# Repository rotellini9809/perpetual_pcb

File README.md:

<h1 align="center">Perpetual — Rocket Avionics PCB</h1>

<p align="center">
  A compact RP2350-based flight computer with an IMU, a barometer, 16 MB of flash for flight logs,<br>
  Bluetooth, four pyrotechnic channels and four servo outputs.
</p>

<p align="center">

</p>

---

> **Part of the Perpetual project**, developed for the
> **Sapienza Rocket Team Training Academy**.
>
> | Repository | Contents |
> |---|---|
> | [Perpetual_training_accademy_avionics](https://github.com/Sapienza-Rocket-Team/Perpetual_training_accademy_avionics) | Main project: overview of the whole system, with the two repositories below as submodules |
> | **perpetual_pcb** (this repository) | Hardware: KiCad schematics, PCB layout and fabrication files |
> | [perpetual_code](https://github.com/rotellini9809/perpetual_code) | Firmware and desktop app |

> [!WARNING]
> This board switches **pyrotechnic channels** directly from the battery. Never connect
> igniters or energetics during bench work, and follow your team's and range's safety rules.
> The board has been assembled and bench-tested, but it is **not flight-qualified or certified for
> any use**. Validate any modified version yourself.

## Contents

- [Hardware overview](#hardware-overview)
- [Gallery](#gallery)
- [Connectors](#connectors)
- [Power](#power)
- [Pyro channels](#pyro-channels)
- [Servo power configuration](#servo-power-configuration)
- [Mechanical](#mechanical)
- [Programming](#programming)
- [Repository layout](#repository-layout)
- [Manufacturing](#manufacturing)
- [Development](#development)
- [Author and license](#author-and-license)

## Hardware overview

| Subsystem | Component | Purpose |
| --- | --- | --- |
| Microcontroller | Waveshare RP2350 Tiny | Processing and peripheral control |
| IMU | LSM6DSV32X | 3-axis acceleration (±32 g) and angular rate |
| Barometer | BMP581 | Pressure and temperature, for altitude |
| Storage | W25Q128JV | 16 MB SPI NOR flash for flight logs |
| Wireless | JDY-34 | Bluetooth link to the Perpetual app |
| Pyro channels | 4 × AO3400A, 74LVC08, TPW4054 | Low-side igniter switches gated by a shared hardware enable, with continuity sensing |
| Servo outputs | 74HCT126 buffer | 4 buffered servo signals, with the supply selectable per channel |
| Power | TPS54302 | 5 V / 3 A buck converter |
| Protection | P-MOSFET and SMBJ15CA TVS | Reverse-polarity and transient protection on the battery input |

The board also provides battery-voltage monitoring, an RGB status LED, a JST connector for
telemetry or I2C, and USB through the RP2350 Tiny flex cable. No magnetometer is fitted.

Flight logs are stored in the onboard flash and downloaded with the
[Perpetual app](https://github.com/rotellini9809/perpetual_code) over **USB or Bluetooth**. No
microSD card is needed.

## Gallery

<table>
  <tr>
    <th>Front</th>
    <th>Back</th>
  </tr>
  <tr>
    <td></td>
    <td></td>
  </tr>
</table>

## Connectors

| Ref | Connector | Signals | Notes |
| --- | --- | --- | --- |
| J6 | AMASS XT30 | Battery `+` / GND | Main power input, 2S–3S LiPo |
| J7–J10 | WAGO 2060 push-in, 2-pole | `+BATT` / switched output | Pyro channels 1–4 |
| J4, J5 | 2×3 pin header, 2.54 mm, right-angle | GND, supply, signal | Servos 1–2 and 3–4. Supply chosen per channel, see [below](#servo-power-configuration) |
| J2 | JST-XH, 3-pin | GND, GP19 (RX / SCL), GP18 (TX / SDA) | Telemetry UART or external I2C |
| J3 | 1×3 pin header, 2.54 mm | GND, +3.3 V, +5 V | Auxiliary power for external devices |
| — | RP2350 Tiny FPC | USB | Programming and data, through the flex cable adapter |

The firmware's GPIO assignment for every signal is listed in the firmware's
[hardware reference](https://github.com/rotellini9809/perpetual_code/blob/main/docs/HARDWARE.md).

## Power

The board is designed to run from a **2S or 3S LiPo** battery (about 6–12.6 V) connected to the
XT30 input. The battery path is:

1. **SMBJ15CA TVS** (D3) across the raw input, for transients. Its 15 V stand-off sets the
   practical upper limit of the input; do not exceed 3S.
2. **P-MOSFET** (Q1, 30P20M) for reverse-polarity protection, giving the protected `+BATT` rail.
3. **TPS54302** buck converter (U4): 5 V rail, up to 3 A.

The RP2350 Tiny provides the 3.3 V rail. Its VSYS input is fed from the 5 V rail through a
**B5817W Schottky** (D1), so USB power cannot back-feed the 5 V rail: on USB alone the MCU and
sensors run, but the servo buffer, servos and pyro channels have no supply. The battery voltage is
measured by the MCU through a 100 kΩ / 24 kΩ divider.

## Pyro channels

Each channel is a WAGO 2060 push-in terminal between `+BATT` and the drain of an **AO3400A**
low-side MOSFET (Q2–Q5). The MOSFET gates are driven by a **74LVC08** AND gate (U6) that combines
the channel pin with a shared **enable** pin: a channel only conducts while both are high, so a
single stuck GPIO cannot fire it. A **TPW4054** 4:1 analog multiplexer (U5) lets the MCU read the
continuity of one channel at a time on an ADC pin.

The firmware's GPIO assignment, firing sequence and continuity thresholds are in the firmware's
[hardware reference](https://github.com/rotellini9809/perpetual_code/blob/main/docs/HARDWARE.md#board-circuits).

## Servo power configuration

Each of the four servo outputs has its own solder bridge on the back of the PCB. The bridge
connects that servo's supply pin either to the regulated **5 V** rail or to the **+BATT** rail.

To configure a channel:

1. Disconnect all power sources.
2. Find the bridge for that channel (**1–4**) using the board markings.
3. Solder **only one side**, toward **5V** or **+BATT**.
4. Check the connection and measure the output voltage before plugging in the servo.

> [!CAUTION]
> With **+BATT** the servo receives the full battery voltage, which must be within the servo's
> rated supply range.

## Mechanical

| Dimension | Value |
| --- | --- |
| Board outline | 50 × 80 mm, 3 mm corner radius |
| Thickness | 1.6 mm, 4 layers |
| Mounting holes | 4 × Ø2.7 mm for M2.5 screws, one per corner |
| Hole position | Centres 3.5 mm from each board edge |
| Hole spacing | 43 × 73 mm, centre to centre |

Pyro terminals sit on one short edge, and the servo headers and XT30 on the other. Leave room
beside the XT30 and the push-in terminals for the cables.

**Bench stand.** A printable stand that holds the board still for IMU calibration and bench tests
is in [`mechanical/bench-stand/`](mechanical/bench-stand). It fixes the board on its four mounting
holes with M2.5 screws.

## Programming

The board is programmed over USB through the **flex cable and USB-C adapter board** supplied
with the Waveshare RP2350 Tiny. The adapter plugs into the FPC connector of the RP2350 Tiny
module, so the main PCB needs no USB connector of its own.

**Perpetual firmware.** The flight computer firmware is in
[perpetual_code](https://github.com/rotellini9809/perpetual_code) and is built and uploaded with
PlatformIO. Connect the adapter with the flex cable (contacts on the correct side), then from that
repository run:

```powershell
pio run -t upload
```

If the board is not detected, hold **BOOT** while plugging in the USB cable, then upload again.
See the [firmware quick start](https://github.com/rotellini9809/perpetual_code#quick-start).

**Your own firmware.** For the MCU, Perpetual is a standard RP2350 Tiny, so you can flash it like
any RP2350 board: with the Pico SDK, Arduino-Pico, MicroPython, or by holding **BOOT** while
plugging in USB and copying a `.uf2` file to the `RP2350` drive that appears. For the pin
assignment, see the firmware's
[hardware reference](https://github.com/rotellini9809/perpetual_code/blob/main/docs/HARDWARE.md),
and for the module, the bootloader and the adapter board, see the
[Waveshare RP2350-Tiny wiki](https://www.waveshare.com/wiki/RP2350-Tiny).

## Repository layout

| Path | Contents |
| --- | --- |
| `perpetual_pcb.kicad_pro` | KiCad project: open this file |
| `perpetual_pcb.kicad_sch` | Top-level schematic, with the `power`, `pyro`, `sensors` and `memory` sub-sheets |
| `perpetual_pcb.kicad_pcb` | PCB layout (4 layers) |
| [`libs/`](libs) | Project symbols, footprints and 3D models |
| [`fabrication_files/`](fabrication_files) | Gerber and drill files |
| [`bom/`](bom) | Interactive BOM (`ibom.html`) |
| [`mechanical/`](mechanical) | 3D-printable parts: the bench stand |
| [`docs/`](docs) | Images, mechanical drawing and component datasheets |

## Manufacturing

Ready-to-order **Gerber and drill files** are in [`fabrication_files/`](fabrication_files), and
also zipped as [`fabrication_files.zip`](fabrication_files.zip). The board is a **4-layer** PCB.
Upload the zip to your PCB manufacturer, and check that the files match the revision you intend
to build.

An interactive bill of materials with component placement is in [`bom/ibom.html`](bom/ibom.html):
download it and open it in a browser.

## Development

Open `perpetual_pcb.kicad_pro` in KiCad 10 to inspect or modify the schematic and the layout.
Before manufacturing or powering a board, review the component ratings, the connections and the
hardware revision.

Contributions and derivatives are welcome within the terms of the license. Please document
meaningful hardware changes and how you validated them.

## Author and license

Designed by **Simone Cargnin** ([@rotellini9809](https://github.com/rotellini9809)) for the
**Sapienza Rocket Team Training Academy**.

Copyright © 2026 Simone Cargnin.

Except where otherwise noted, the original hardware design files and documentation in this
repository are licensed under
[Creative Commons Attribution-NonCommercial-ShareAlike 4.0 International](LICENSE).

When sharing these files or adaptations, give appropriate credit, link to the license and
indicate your changes. Shared adaptations must use CC BY-NC-SA 4.0, a later version, or a
BY-NC-SA Compatible License.

Suggested attribution:
“Based on Perpetual by Simone Cargnin, developed for the Sapienza Rocket Team Training Academy.”
Original project: https://github.com/rotellini9809/perpetual_pcb

Third-party symbols, footprints, models and other assets keep their own licenses.

For commercial permissions, contact rotellini9809@gmail.com.

If you use Perpetual in research, please let me know at the address above. This is a voluntary
request, not a license condition.

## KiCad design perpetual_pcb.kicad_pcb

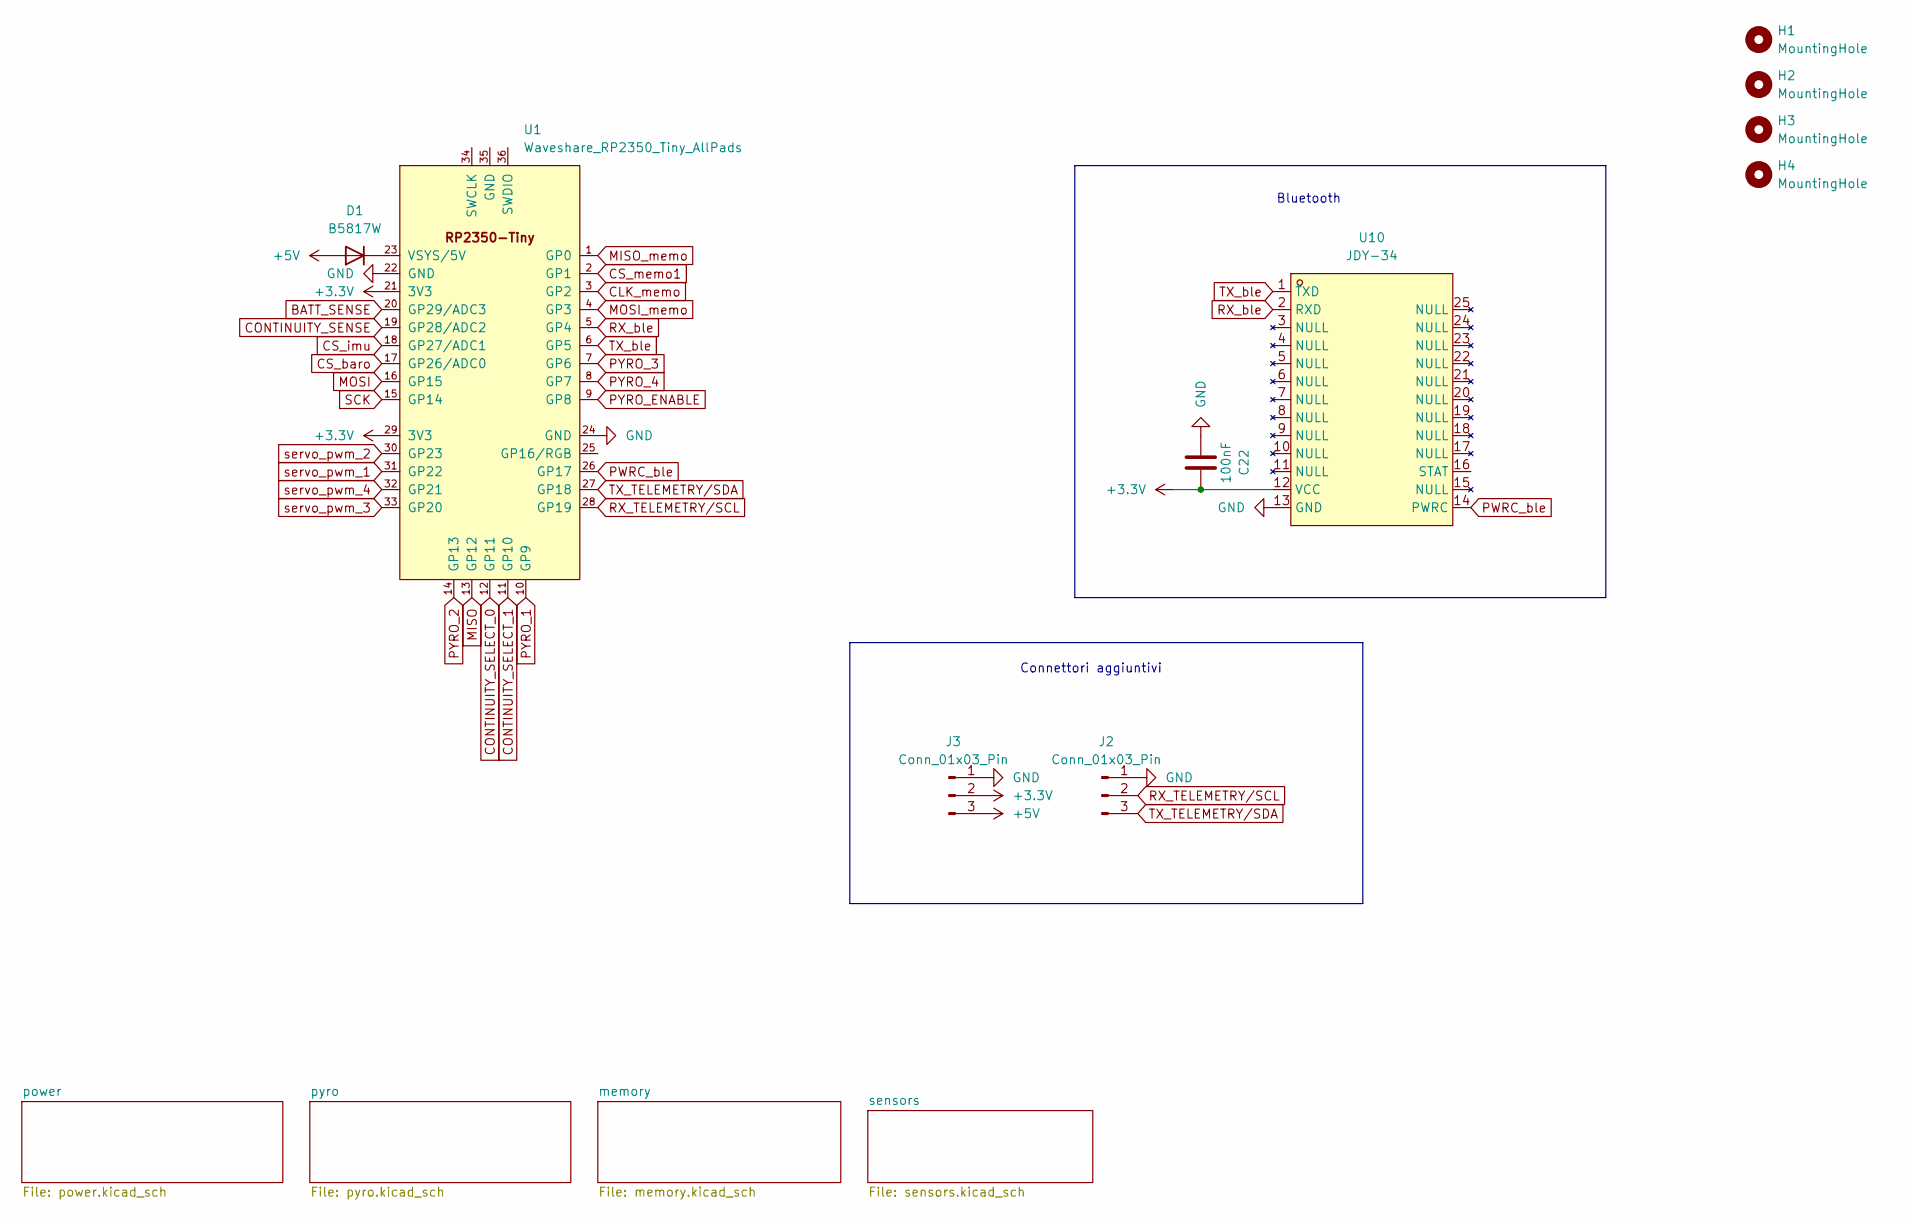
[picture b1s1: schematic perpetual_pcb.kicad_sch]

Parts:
C22: 100nF; C_0603_1608Metric
D1: B5817W; D_SOD-123
H1, H2, H3, H4: MountingHole; MountingHole_2.7mm_M2.5
J2: Conn_01x03_Pin; JST_XH_B3B-XH-A_1x03_P2.50mm_Vertical
J3: Conn_01x03_Pin; PinHeader_1x03_P2.54mm_Vertical
U1: Waveshare_RP2350_Tiny_AllPads; Waveshare_RP2350_Tiny_AllPads_36Pin
U10: JDY-34; BULETM-SMD_JDY-34; MPN JDY-34

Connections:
+3.3V: C22.1, J3.2, U1.21 (3V3), U1.29 (3V3), U10.12 (VCC); also elsewhere on the board
+5V: D1.2 (A), J3.3; also elsewhere on the board
BATT_SENSE: U1.20 (GP29/ADC3); also elsewhere on the board
CLK_memo: U1.3 (GP2); also elsewhere on the board
CONTINUITY_SELECT_0: U1.12 (GP11); also elsewhere on the board
CONTINUITY_SELECT_1: U1.11 (GP10); also elsewhere on the board
CONTINUITY_SENSE: U1.19 (GP28/ADC2); also elsewhere on the board
CS_baro: U1.17 (GP26/ADC0); also elsewhere on the board
CS_imu: U1.18 (GP27/ADC1); also elsewhere on the board
CS_memo1: U1.2 (GP1); also elsewhere on the board
GND: C22.2, J2.1, J3.1, U1.22 (GND), U1.24 (GND), U10.13 (GND); also elsewhere on the board
MISO: U1.13 (GP12); also elsewhere on the board
MISO_memo: U1.1 (GP0); also elsewhere on the board
MOSI: U1.16 (GP15); also elsewhere on the board
MOSI_memo: U1.4 (GP3); also elsewhere on the board
unnamed: D1.1 (K), U1.23 (VSYS/5V)
PWRC_ble: U1.26 (GP17), U10.14 (PWRC)
PYRO_1: U1.10 (GP9); also elsewhere on the board
PYRO_2: U1.14 (GP13); also elsewhere on the board
PYRO_3: U1.7 (GP6); also elsewhere on the board
PYRO_4: U1.8 (GP7); also elsewhere on the board
PYRO_ENABLE: U1.9 (GP8); also elsewhere on the board
RX_TELEMETRY/SCL: J2.2, U1.28 (GP19)
RX_ble: U1.5 (GP4), U10.2 (RXD)
SCK: U1.15 (GP14); also elsewhere on the board
TX_TELEMETRY/SDA: J2.3, U1.27 (GP18)
TX_ble: U1.6 (GP5), U10.1 (TXD)
servo_pwm_1: U1.31 (GP22); also elsewhere on the board
servo_pwm_2: U1.30 (GP23); also elsewhere on the board
servo_pwm_3: U1.33 (GP20); also elsewhere on the board
servo_pwm_4: U1.32 (GP21); also elsewhere on the board

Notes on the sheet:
Bluetooth
Connettori aggiuntivi

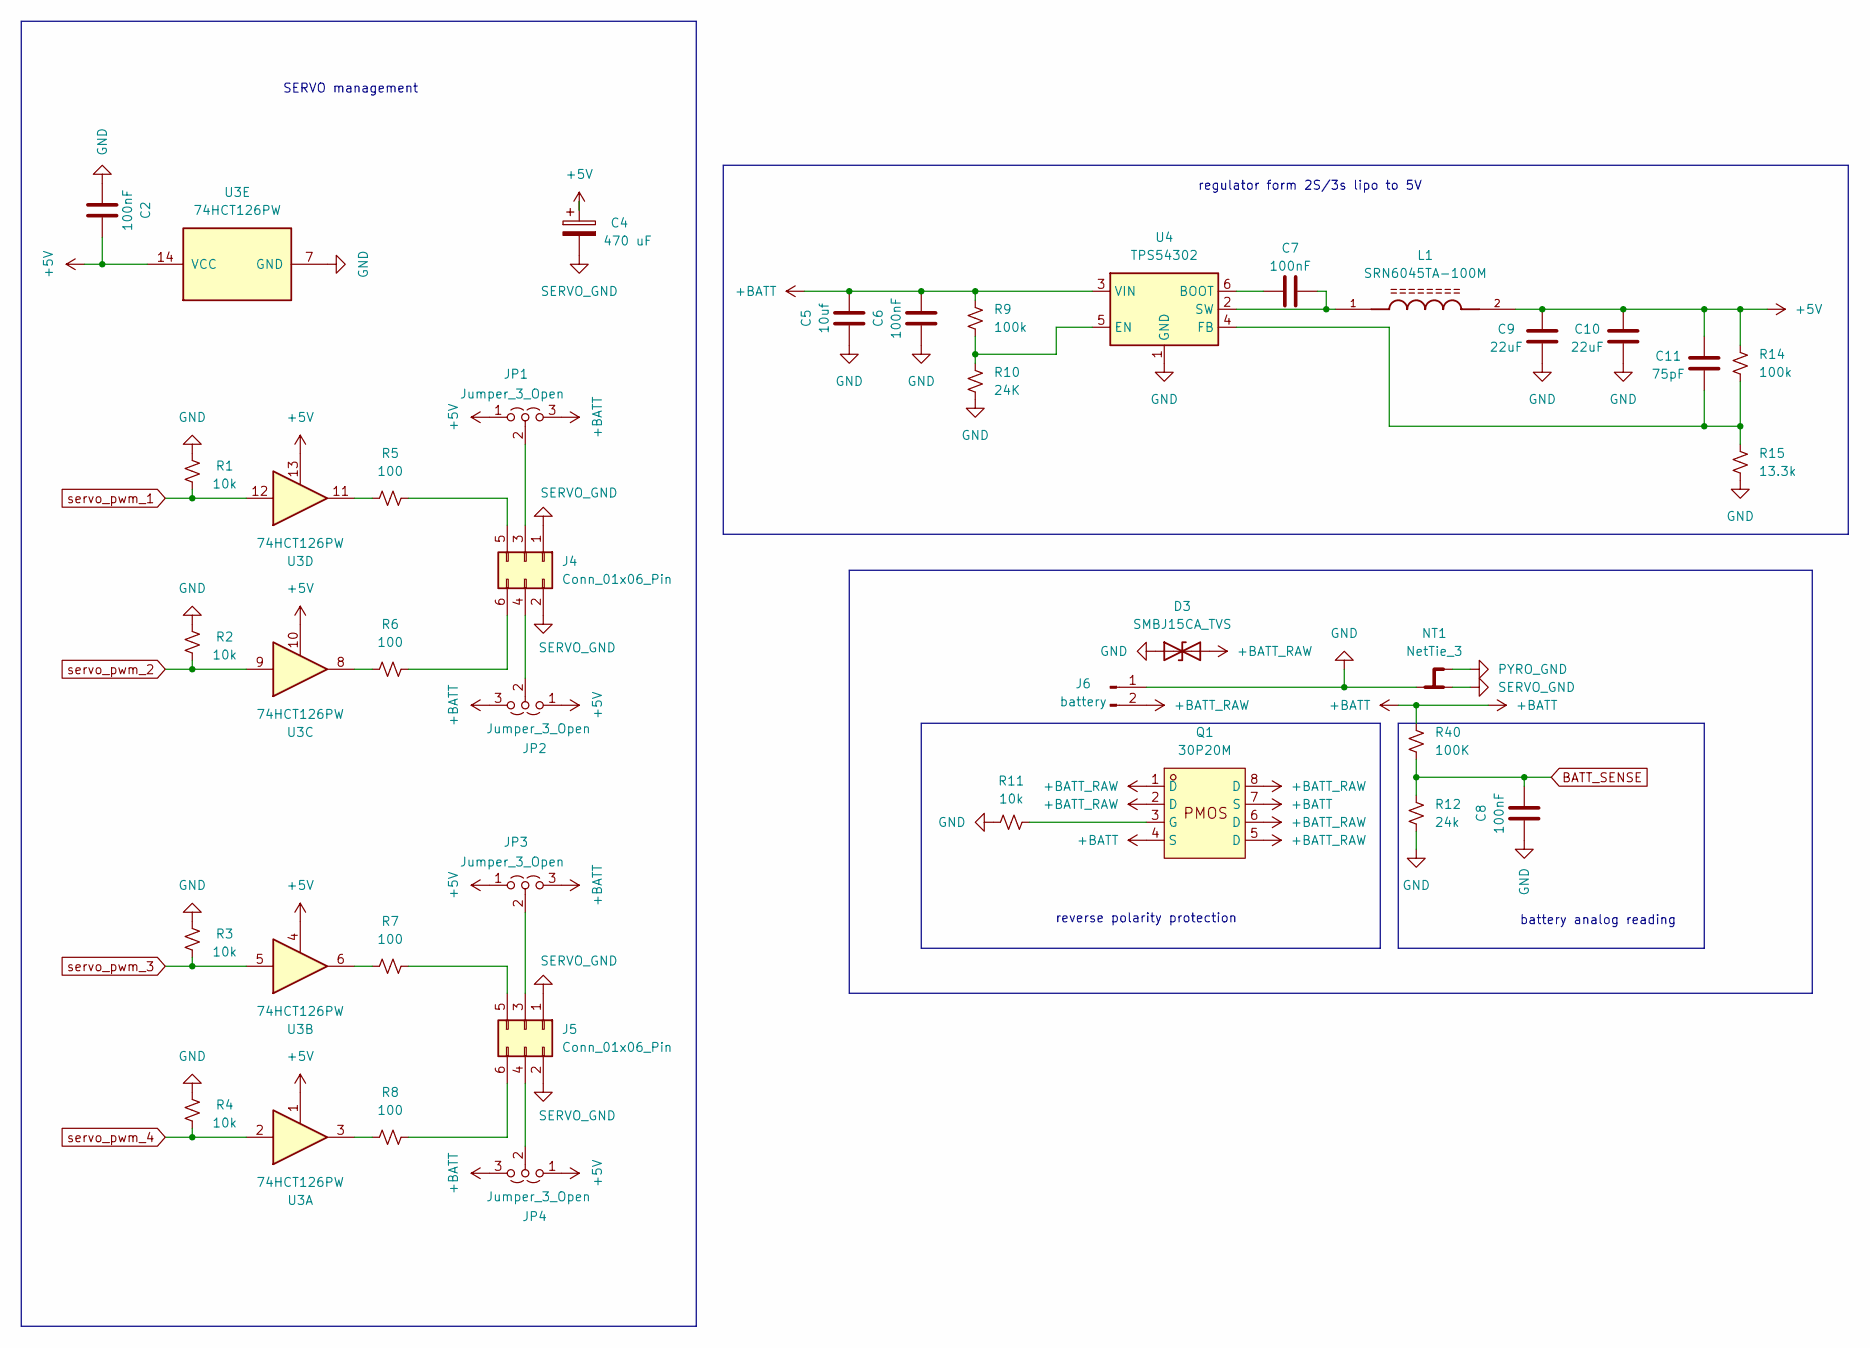
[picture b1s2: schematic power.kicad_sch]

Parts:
C2, C6, C7, C8: 100nF; C_0603_1608Metric
C4: 470 uF; C_Elec_8x10.2; LCSC part C141429
C5: 10uf; C_1206_3216Metric
C9, C10: 22uF; C_1206_3216Metric
C11: 75pF; C_0603_1608Metric
D3: SMBJ15CA_TVS; D_SMB
J4, J5: Conn_01x06_Pin; PinHeader_2x03_P2.54mm_Horizontal
J6: battery; AMASS_XT30PW-M_1x02_P2.50mm_Horizontal
JP1, JP2, JP3, JP4: Jumper_3_Open; SolderJumper-3_P1.3mm_Open_RoundedPad1.0x1.5mm
L1: SRN6045TA-100M
NT1: NetTie_3; NetTie-3_SMD_Pad2.0mm
Q1: 30P20M; MPN 30P20M; LCSC Part C7471110
R1, R2, R3, R4, R11: 10k; R_0603_1608Metric
R5, R6, R7, R8: 100; R_0603_1608Metric
R9, R14: 100k; R_0603_1608Metric
R10: 24K; R_0603_1608Metric
R12: 24k; R_0603_1608Metric
R15: 13.3k; R_0603_1608Metric
R40: 100K; R_0603_1608Metric
U3: 74HCT126PW; TSSOP-14_4.4x5mm_P0.65mm
U4: TPS54302; SOT-23-6

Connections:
+5V: C2.1, C4.1, C9.1, C10.1, C11.1, JP1.1 (A), JP2.1 (A), JP3.1 (A), JP4.1 (A), L1.2, R14.1, U3.1, U3.4, U3.10, U3.13, U3.14 (VCC); also elsewhere on the board
+BATT: C5.1, C6.1, JP1.3 (B), JP2.3 (B), JP3.3 (B), JP4.3 (B), Q1.4 (S), Q1.7 (S), R9.1, R40.1, U4.3 (VIN); also elsewhere on the board
+BATT_RAW: D3.2 (A2), J6.2, Q1.1 (D), Q1.2 (D), Q1.5 (D), Q1.6 (D), Q1.8 (D)
BATT_SENSE: C8.1, R12.1, R40.2; also elsewhere on the board
GND: C2.2, C5.2, C6.2, C8.2, C9.2, C10.2, D3.1 (A1), J6.1, NT1.2, R1.1, R2.1, R3.1, R4.1, R10.2, R11.1, R12.2, R15.2, U3.7 (GND), U4.1 (GND); also elsewhere on the board
unnamed: J4.3, JP1.2 (C)
unnamed: J4.4, JP2.2 (C)
unnamed: J4.5, R5.2
unnamed: J4.6, R6.2
unnamed: J5.3, JP3.2 (C)
unnamed: J5.4, JP4.2 (C)
unnamed: J5.5, R7.2
unnamed: J5.6, R8.2
unnamed: Q1.3 (G), R11.2
unnamed: R5.1, U3.11
unnamed: R6.1, U3.8
unnamed: R7.1, U3.6
unnamed: R8.1, U3.3
unnamed: C7.2, U4.6 (BOOT)
unnamed: R9.2, R10.1, U4.5 (EN)
unnamed: C11.2, R14.2, R15.1, U4.4 (FB)
unnamed: C7.1, L1.1, U4.2 (SW)
PYRO_GND: NT1.3; also elsewhere on the board
SERVO_GND: C4.2, J4.1, J4.2, J5.1, J5.2, NT1.1
servo_pwm_1: R1.2, U3.12; also elsewhere on the board
servo_pwm_2: R2.2, U3.9; also elsewhere on the board
servo_pwm_3: R3.2, U3.5; also elsewhere on the board
servo_pwm_4: R4.2, U3.2; also elsewhere on the board

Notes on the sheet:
regulator form 2S/3s lipo to 5V
reverse polarity protection
SERVO management
battery analog reading

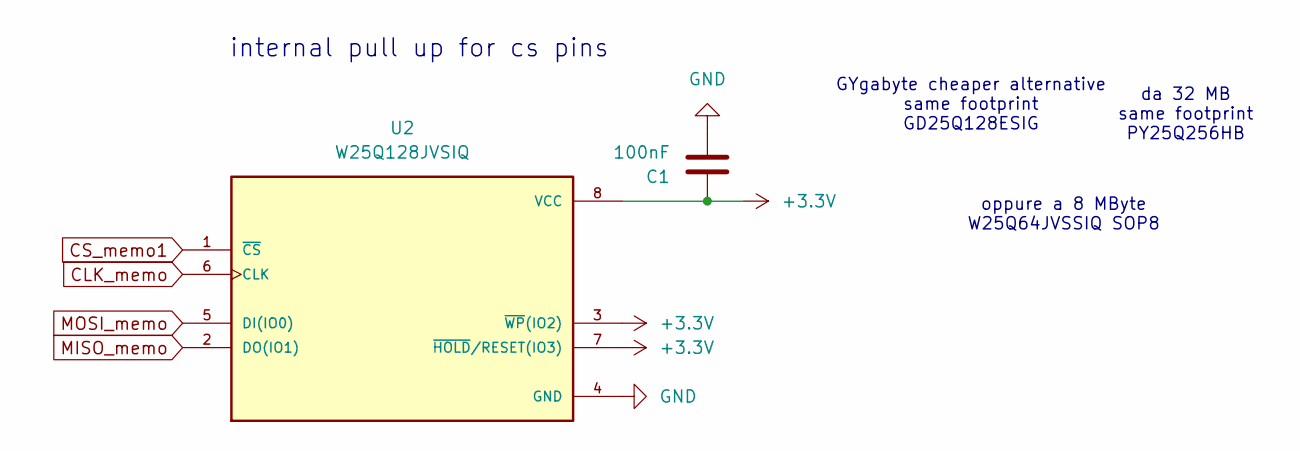
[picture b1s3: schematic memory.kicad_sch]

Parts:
C1: 100nF; C_0603_1608Metric
U2: W25Q128JVSIQ; SOIC127P790X216-8N

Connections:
+3.3V: C1.1, U2.3 (~WP(IO2)), U2.7 (~HOLD/RESET(IO3)), U2.8 (VCC); also elsewhere on the board
CLK_memo: U2.6 (CLK); also elsewhere on the board
CS_memo1: U2.1 (~CS); also elsewhere on the board
GND: C1.2, U2.4 (GND); also elsewhere on the board
MISO_memo: U2.2 (DO(IO1)); also elsewhere on the board
MOSI_memo: U2.5 (DI(IO0)); also elsewhere on the board

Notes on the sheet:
internal pull up for cs pins
oppure a 8 MByte W25Q64JVSSIQ SOP8
GYgabyte cheaper alternative same footprint GD25Q128ESIG
da 32 MB same footprint PY25Q256HB

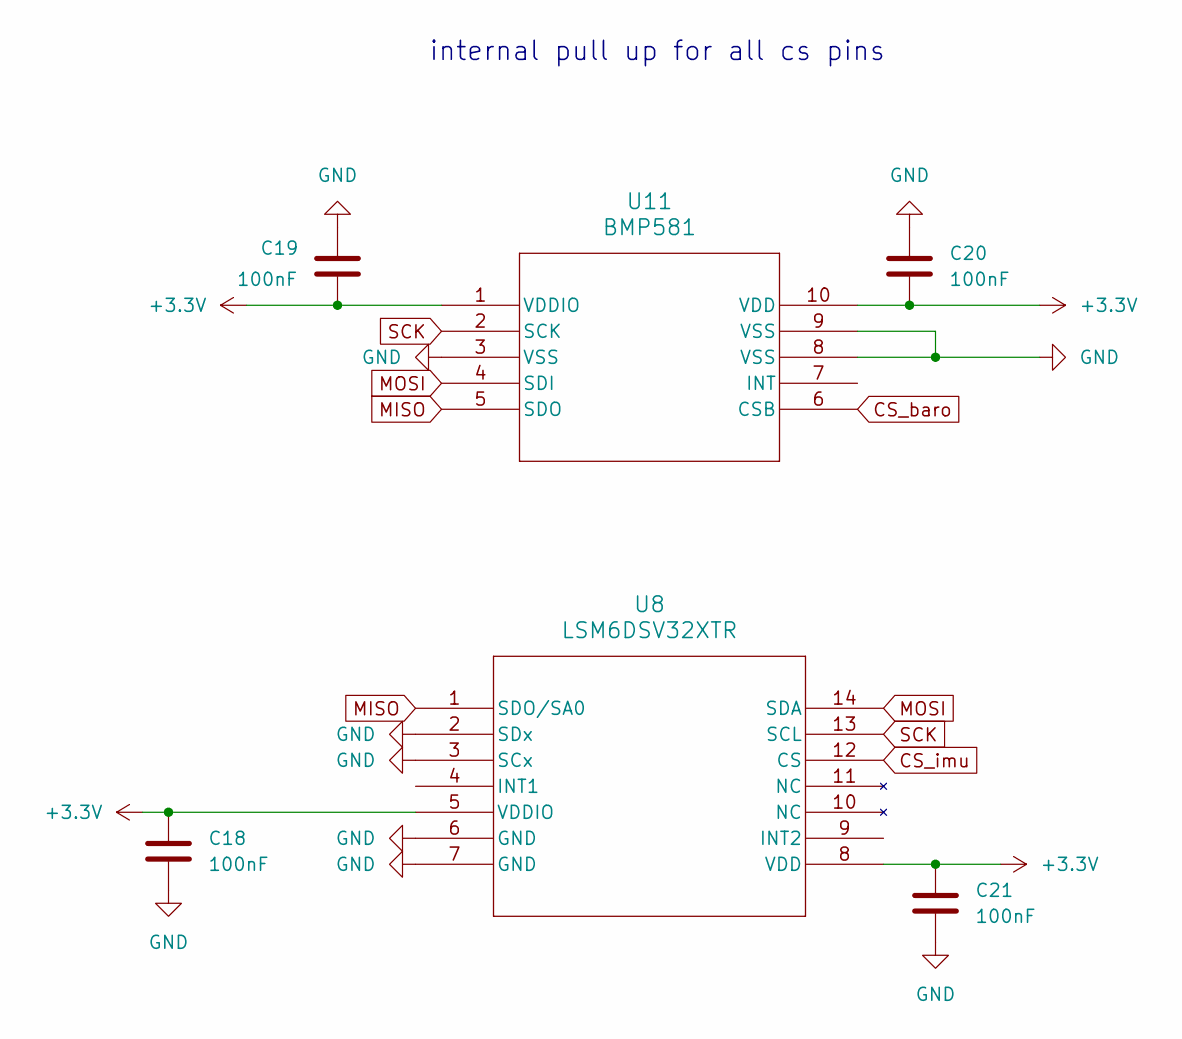
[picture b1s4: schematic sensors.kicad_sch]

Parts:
C18, C19, C20, C21: 100nF; C_0603_1608Metric
U8: LSM6DSV32XTR; LGA-14L_2P5X3X0P83_STM-M
U11: BMP581; QFN10_BMP581_BOS-M

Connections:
+3.3V: C18.1, C19.2, C20.2, C21.1, U8.5 (VDDIO), U8.8 (VDD), U11.1 (VDDIO), U11.10 (VDD); also elsewhere on the board
CS_baro: U11.6 (CSB); also elsewhere on the board
CS_imu: U8.12 (CS); also elsewhere on the board
GND: C18.2, C19.1, C20.1, C21.2, U8.2 (SDx), U8.3 (SCx), U8.6 (GND), U8.7 (GND), U11.3 (VSS), U11.8 (VSS), U11.9 (VSS); also elsewhere on the board
MISO: U8.1 (SDO/SA0), U11.5 (SDO); also elsewhere on the board
MOSI: U8.14 (SDA), U11.4 (SDI); also elsewhere on the board
SCK: U8.13 (SCL), U11.2 (SCK); also elsewhere on the board

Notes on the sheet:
internal pull up for all cs pins

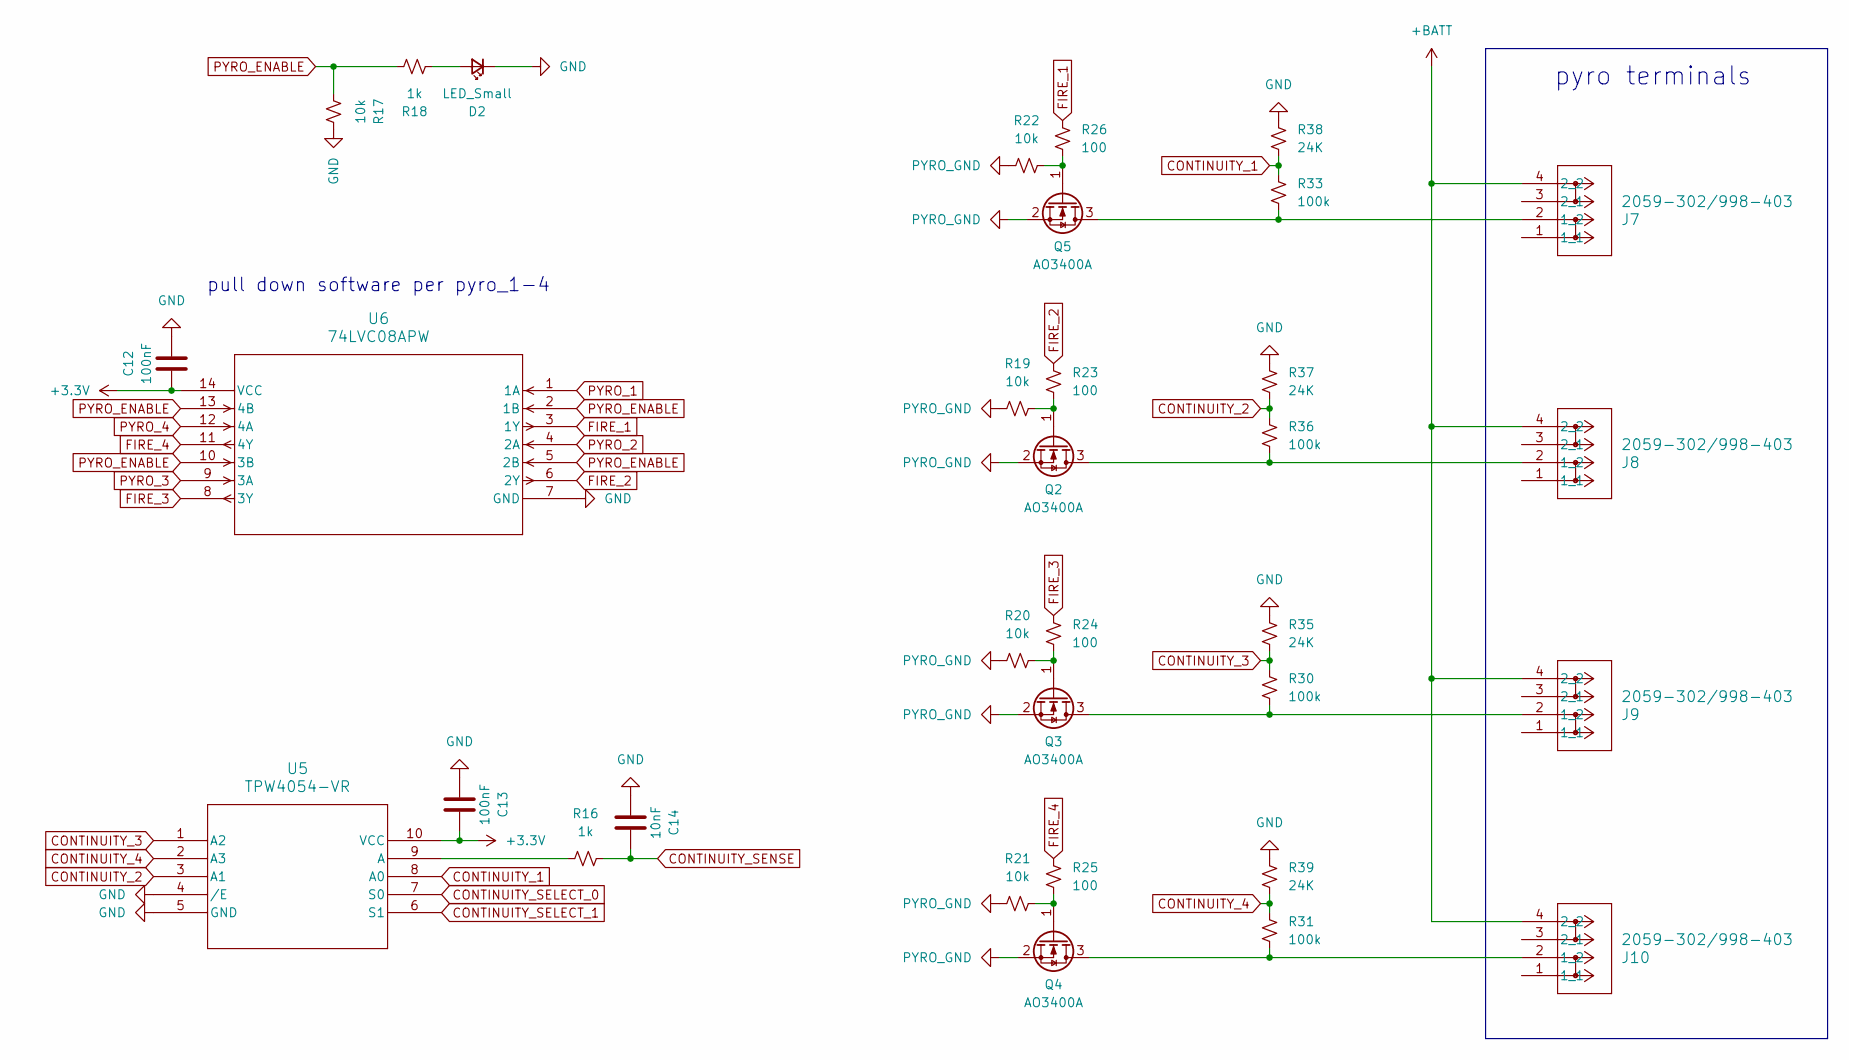
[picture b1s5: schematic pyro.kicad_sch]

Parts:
C12, C13: 100nF; C_0603_1608Metric
C14: 10nF; C_0603_1608Metric
D2: LED_Small; LED_0603_1608Metric
J7, J8, J9, J10: 2059-302/998-403; CONN2_2060-452&slash_998-404_WAG
Q2, Q3, Q4, Q5: AO3400A; SOT-23
R16, R18: 1k; R_0603_1608Metric
R17, R19, R20, R21, R22: 10k; R_0603_1608Metric
R23, R24, R25, R26: 100; R_0603_1608Metric
R30, R31, R33, R36: 100k; R_0603_1608Metric
R35, R37, R38, R39: 24K; R_0603_1608Metric
U5: TPW4054-VR; MSOP-10_TPK
U6: 74LVC08APW; SOT402-1_NXP

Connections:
+3.3V: C12.2, C13.2, U5.10 (VCC), U6.14 (VCC); also elsewhere on the board
+BATT: J7.4 (2_2), J8.4 (2_2), J9.4 (2_2), J10.4 (2_2); also elsewhere on the board
CONTINUITY_1: R33.1, R38.2, U5.8 (A0)
CONTINUITY_2: R36.1, R37.2, U5.3 (A1)
CONTINUITY_3: R30.1, R35.2, U5.1 (A2)
CONTINUITY_4: R31.1, R39.2, U5.2 (A3)
CONTINUITY_SELECT_0: U5.7 (S0); also elsewhere on the board
CONTINUITY_SELECT_1: U5.6 (S1); also elsewhere on the board
CONTINUITY_SENSE: C14.2, R16.2; also elsewhere on the board
FIRE_1: R26.1, U6.3 (1Y)
FIRE_2: R23.1, U6.6 (2Y)
FIRE_3: R24.1, U6.8 (3Y)
FIRE_4: R25.1, U6.11 (4Y)
GND: C12.1, C13.1, C14.1, D2.1 (K), R17.1, R35.1, R37.1, R38.1, R39.1, U5.4 (/E), U5.5 (GND), U6.7 (GND); also elsewhere on the board
unnamed: D2.2 (A), R18.1
unnamed: J7.2 (1_2), Q5.3 (D), R33.2
unnamed: J8.2 (1_2), Q2.3 (D), R36.2
unnamed: J9.2 (1_2), Q3.3 (D), R30.2
unnamed: J10.2 (1_2), Q4.3 (D), R31.2
unnamed: Q2.1 (G), R19.2, R23.2
unnamed: Q3.1 (G), R20.2, R24.2
unnamed: Q4.1 (G), R21.2, R25.2
unnamed: Q5.1 (G), R22.2, R26.2
unnamed: R16.1, U5.9 (A)
PYRO_1: U6.1 (1A); also elsewhere on the board
PYRO_2: U6.4 (2A); also elsewhere on the board
PYRO_3: U6.9 (3A); also elsewhere on the board
PYRO_4: U6.12 (4A); also elsewhere on the board
PYRO_ENABLE: R17.2, R18.2, U6.2 (1B), U6.5 (2B), U6.10 (3B), U6.13 (4B); also elsewhere on the board
PYRO_GND: Q2.2 (S), Q3.2 (S), Q4.2 (S), Q5.2 (S), R19.1, R20.1, R21.1, R22.1; also elsewhere on the board

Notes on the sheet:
pyro terminals
pull down software per pyro_1-4

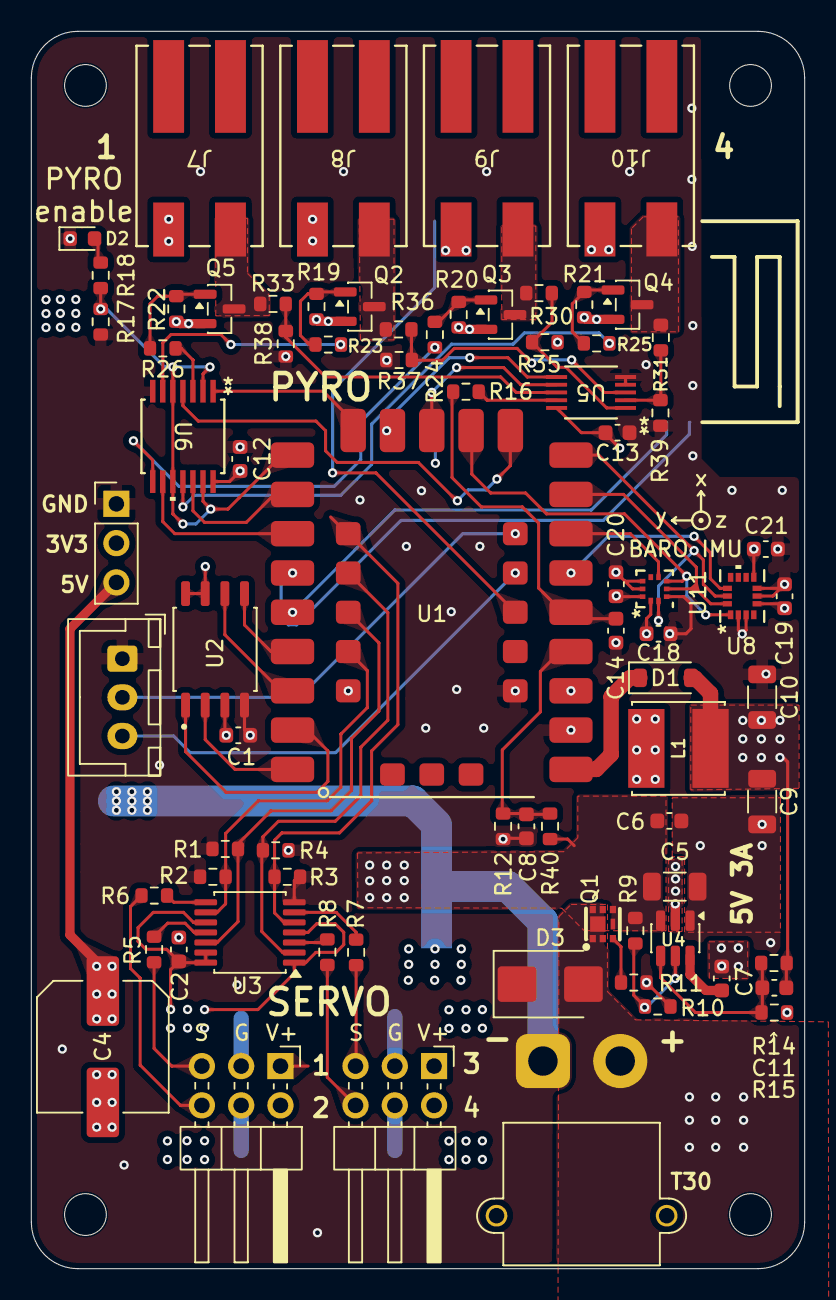
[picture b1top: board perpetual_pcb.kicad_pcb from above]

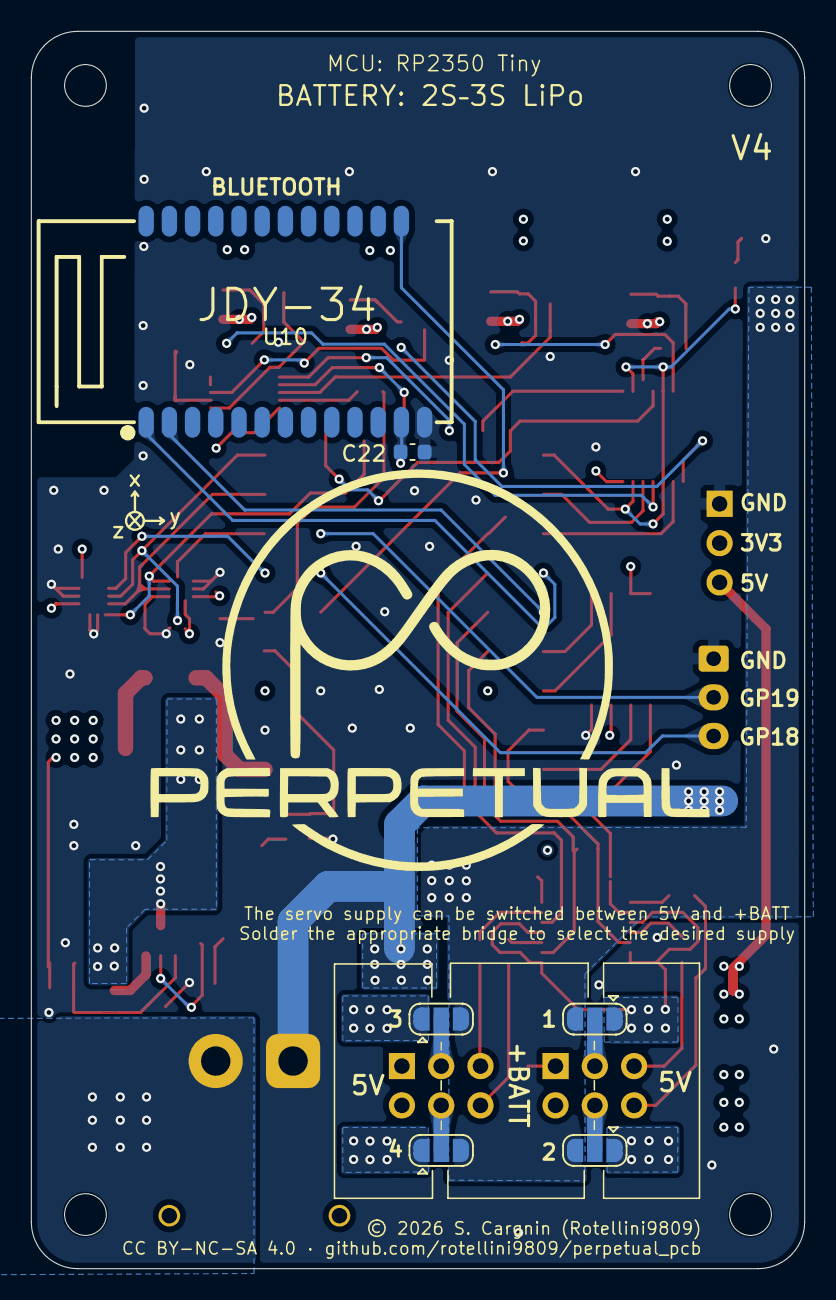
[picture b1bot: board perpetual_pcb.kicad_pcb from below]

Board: 4 copper layers, 50.0 x 80.0 mm, 88 parts (7 on the bottom side), 70 nets.

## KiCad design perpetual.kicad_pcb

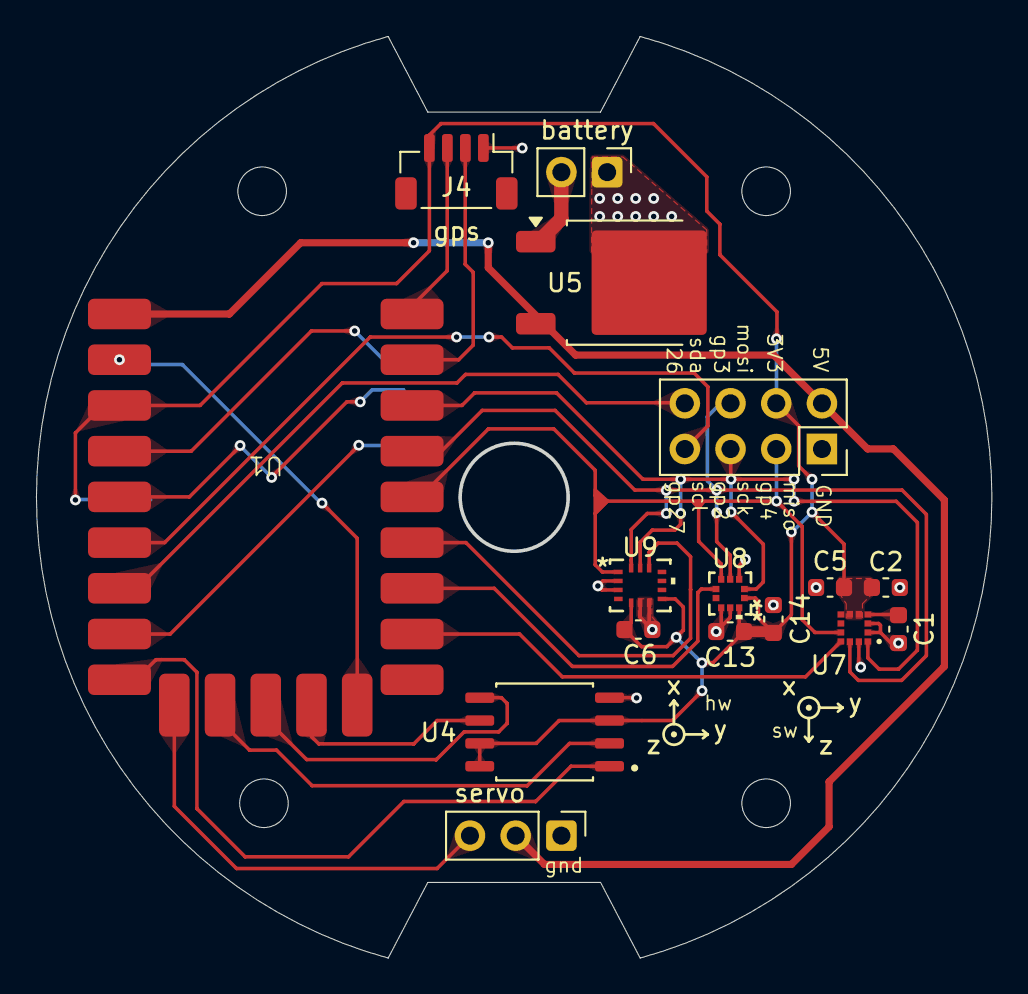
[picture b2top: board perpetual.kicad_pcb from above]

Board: 2 copper layers, 53.1 x 51.2 mm, 21 parts (1 on the bottom side), 24 nets.

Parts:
B1: JDY-23_HandSoldering
C1, C5, C6, C13, C14: 100nF; C_0603_1608Metric
C2: 1nF; C_0603_1608Metric
H1, H1#2, H2, H3: MountingHole; MountingHole_2.7mm_M2.5
J1: battery; PinHeader_1x02_P2.54mm_Vertical
J2: SERVO; PinHeader_1x03_P2.54mm_Vertical
J3: Conn_02x04_Counter_Clockwise; PinHeader_2x04_P2.54mm_Vertical
J4: GPS; JST_SH_BM04B-SRSS-TB_1x04-1MP_P1.00mm_Vertical
U1: RP2350-Tiny; Waveshare RP2350-Tiny
U4: W25Q64JVSSIQ; SOIC127P790X216-8N
U5: MC7805BDTRKG; TO-252-2
U7: LIS3MDL; LGA-12_2X2X1_STM
U8: BMP390; 10LGA_2X2X0p75_BOS
U9: LSM6DSO32TR; LGA-14L_2P5X3X0P83_STM

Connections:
+3.3V: B1.1 (VCC), C2.1, C5.1, C6.1, C13.1, C14.1, J3.3, J4.4, U1.16 (3V3), U4.3 (~WP(IO2)), U4.7 (~HOLD/RESET(IO3)), U4.8 (VCC), U7.5 (VDD), U7.6 (VDD_IO), U8.1 (VDDIO), U8.10 (VDD), U9.5 (VDDIO), U9.8 (VDD)
+5V: J2.2, J3.2, U1.18 (5V), U5.3 (OUTPUT)
+BATT: J1.2, U5.1 (INPUT)
CLK_memo: U1.10 (GPIO10), U4.6 (CLK)
CS_baro: U1.6 (GPIO6), U8.6 (CSB)
CS_imu: U1.5 (GPIO5), U9.12 (CS)
CS_mag: U1.7 (GPIO7), U7.10 (CS)
CS_memo1: U1.14 (GPIO14), U4.1 (~CS)
GND: B1.24 (GND), C1.2, C2.2, C5.2, C6.2, C13.2, C14.2, J1.1, J2.1, J3.1, J4.1, U1.17 (GND), U4.4 (GND), U5.2 (GROUND), U7.2 (RES), U7.3 (GND), U7.12 (RES), U8.3 (VSS), U8.8 (VSS), U8.9 (VSS), U9.2 (SDx), U9.3 (SCx), U9.6 (GND), U9.7 (GND)
GPIO_SCL: J3.8, U1.27 (GPIO27_ADC1)
GPIO_SDA: J3.7, U1.26 (GPIO26_ADC0)
MISO: J3.4, U1.4 (GPIO4), U7.9 (SDO/SA1), U8.5 (SDO), U9.1 (SDO/SA0)
MISO_memo: U1.12 (GPIO12), U4.2 (DO(IO1))
MOSI: J3.5, U1.3 (GPIO3), U7.11 (SDA/SDI/SDO), U8.4 (SDI), U9.14 (SDA)
MOSI_memo: U1.11 (GPIO11), U4.5 (DI(IO0))
unnamed: C1.1, U7.4 (C1)
PWRC_ble: B1.22 (PWRC), U1.15 (GPIO15)
RX_GPS: J4.3, U1.0 (GPIO0)
RX_ble: B1.20 (RXD), U1.28 (GPIO28_ADC2)
SCK: J3.6, U1.2 (GPIO2), U7.1 (SCL/SPC), U8.2 (SCK), U9.13 (SCL)
TX_GPS: J4.2, U1.1 (GPIO1)
TX_ble: B1.19 (TXD), U1.29 (GPIO29_ADC3)
conn_status_ble: B1.6 (STAT), U1.9 (GPIO9)
servo_pwm: J2.3, U1.13 (GPIO13)

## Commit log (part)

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2025-11-10 tanta roba
2025-11-10 della roba
2025-11-10 fraaa
2025-12-21 mado le skilll
2025-12-22 robaa
2026-01-18 tutte cose
2026-01-18 aggiunte teardrop
2026-01-18 ultime robe fixate
2026-01-19 last fix giuro
2026-02-16 fgdxfxdv

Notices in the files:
README.md:
License: CC BY-NC-SA 4.0
perpetual_pcb.kicad_pcb:
© 2026 S. Cargnin (Rotellini9809)
CC BY-NC-SA 4.0 · github.com/rotellini9809/perpetual_pcb
